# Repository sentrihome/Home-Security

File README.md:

# Home Security System — Full Architecture

Status: design draft — SoftAP shipping; Pi hub (`pi_hub`) barebones in repo; live/clips/Drive stubs pending full impl
Scope: end-to-end system — ESP32 hardware, provisioning, sensor pairing, security model, protocol specs, Pi/app/cloud product layer (alerts, live, clips), and known open items.
Merges: original ESP32 hardware architecture + `Local-First Architecture Storyboard` (mobile/, Pi, Tailscale, FCM/ntfy, Drive).
Pi software: Python SoftAP gate + one `pi_hub` process (not the retired Node `rasberry_pi_app` / cloud stack) — see **D20** and §13.

---
## Branch Naming Convention
Three types of tasks:
1. Rasberry Pi pie
2. ESP esp
3. Mobile app mob
Name of person working: firstname
Bitesized task: task

So the branch name will be: type-firstname-task

## Quick nav

| Section | Contents |
|---|---|
| [1](#1-system-overview) | System overview & diagram |
| [2](#2-hardware--component-roles) | Every component's role |
| [2.1](#21-esp32-architecture-diagram) | ESP32 hardware diagram — networks, UART, credential flow |
| [3](#3-decision-log) | Locked product choices |
| [4](#4-console-provisioning-flow) | Phone → console WROOM → S3 → home WiFi |
| [5](#5-sensor-pairing-flow) | Phone → sensor → console WROOM |
| [6](#6-default-ap-credentials-setup-time) | Anti-eavesdropping setup credentials |
| [7](#7-credential--key-model) | The three secrets, who holds what |
| [8](#8-failure-handling-provisioning) | WiFi connect failure/retry |
| [9](#9-uart-protocol-wroom--s3) | Frame format, command set |
| [10](#10-setup-ap-encryption) | WPA2 requirement on all setup APs |
| [11](#11-psk-recovery--backup) | Pi as PSK backup, tied to §16 |
| [12](#12-reboot--reconnect-behavior) | Console/S3/sensor reboot handling |
| [13](#13-pi-setup--product-hub) | SoftAP gate → `pi_hub` (live/clips); how it works & deploy |
| [14](#14-intruder-alerts-android-fcm--ios-ntfysh) | FCM (Android), ntfy.sh (iOS) |
| [15](#15-on-demand-livestream-tailscale) | Live only while app is open |
| [16](#16-pi--s3-link-confirmed-endpoints-transport-tbd) | Confirmed Pi↔S3 endpoints; transport still TBD |
| [17](#17-clips-pi-cache--google-drive) | Clip capture, cache, upload, playback |
| [18](#18-google-token-handoff) | OAuth refresh token to Pi |
| [18.1](#181-what-the-pi-needs-phone--pi-contract) | Locked JSON contract for the phone handoff |
| [19](#19-motion-event-pipeline-partially-resolved) | Camera confirmed Pi-only; alert-pipeline scope still open |
| [20](#20-arm--disarm-state-machine) | State ownership, authorization, entry/exit, sensor behavior |
| [21](#21-out-of-scope) | Explicit non-goals |
| [22](#22-open-items) | Full consolidated list |
| [23](#23-physical--manufacturing-notes) | Enclosure & label handling |

---

## 1. System Overview

Three physical subsystems, tied together by two links that are fully specified and one that is not yet:

```mermaid
flowchart TB
  subgraph sensors [Sensor Network]
    Sen1[Sensor WROOM]
    Sen2[Sensor WROOM]
  end

  subgraph console [Central Console]
    CW[Console WROOM<br/>AP + hub]
    S3[ESP32-S3<br/>station, display]
    Sen1 -->|WiFi, sensor_key auth| CW
    Sen2 -->|WiFi, sensor_key auth| CW
    CW <-->|UART, framed| S3
  end

  subgraph home [Home LAN / Cloud Layer]
    Pi[Raspberry Pi<br/>static IP, health, alerts, live, clips]
    FCM[FCM - Android]
    Ntfy[ntfy.sh - iOS]
    Drive[Google Drive]
    TS[Tailscale]
    S3 -.->|§16, endpoints confirmed<br/>transport TBD| Pi
    Pi -->|motion| FCM
    Pi -->|motion| Ntfy
    Pi --> Drive
    Pi <--> TS
  end

  subgraph phone [Mobile App]
    App[React Native app]
    FCM -->|tap| App
    Ntfy -->|tap/open| App
    App <-->|setup, live, clips| Pi
    App -.->|setup| CW
  end
```

**Fully specified today:** sensor ↔ console WROOM (WiFi + `sensor_key`), console WROOM ↔ S3 (UART, framed), phone ↔ Pi (SoftAP setup, health check, Tailscale, OAuth handoff, FCM/ntfy targets, Drive playback).

**Confirmed but not yet fully specified:** S3 ↔ Pi. The endpoints are settled — this is a direct Pi↔S3 link, not routed through the WROOM (§16, §20) — but the transport mechanism (static IP / mDNS / hybrid), framing, and auth are still open. Everything downstream of it (motion-triggered alerts reaching the Pi, PSK backup reaching the Pi, the PIN-set flow) depends on this transport being finalized.

---

## 2. Hardware & Component Roles

| Component | Role | WiFi / Network Mode | Responsibilities |
|---|---|---|---|
| ESP32-S3 | Central console | Station (home WiFi) | Display, keypad (PIN entry for disarm — see §20), stores home WiFi creds, stores sensor keys, **stores the disarm PIN in NVS**, relays credentials/status to console WROOM over UART. Motion/event relay toward Pi confirmed required — see §16, §20. |
| ESP32-WROOM (console-side) | Sensor hub / pairing surface | Access Point (persistent, currently `"espwifi"` — SSID string is not a hard spec requirement, any static value works) | Hosts sensor network, relays sensor data to S3 via UART, validates sensor auth (`sensor_key`), generates pairing credentials and the sensor-network PSK |
| ESP32-WROOM (sensor units) | Sensors | Station → connects to console WROOM's AP | Motion/door/etc. detection, sends events authenticated with `sensor_key`. One of two motion-alert triggers, alongside the Pi's camera detector — see §19. |
| Raspberry Pi | Setup relay, PSK backup, product hub | AP (setup only) → Station (post-setup, static IP `192.168.0.236`) | **Initializes first, before console provisioning — see §4, §13.** SoftAP then **`pi_hub`** on `:4000`. Owns the camera; OpenCV person detection (§19); FCM/ntfy alerts; WebRTC live; Drive clip upload; PSK backup pending §16 |
| Mobile App (React Native, `mobile/`) | Orchestrator / client | N/A | Walks the user through both the Pi setup flow and the console/sensor provisioning flow, holds home WiFi creds in memory only during setup, stores the sensor-network PSK for future pairing, saves the Pi host, registers for push (FCM/ntfy), handles Google OAuth and hands the refresh token to the Pi, plays live (via Tailscale) and clips (via Drive) |

**Confirmed: no camera on any ESP32.** The camera is Pi-attached only. It is no longer monitoring-only: the Pi runs OpenCV person detection on the camera feed as a second, independent motion-alert trigger alongside the ESP32 sensor network. See §19.

**Confirmed: the console has a physical keypad**, used for PIN entry on disarm (§20). **The PIN itself is stored in S3 NVS**, not on the Pi — this creates a flagged tension with the Pi-as-state-authority decision, see §20. **No local audio/siren hardware is planned for initial release** — the console is display + keypad only; Bluetooth speaker support (as a post-launch siren option) is roadmap, not v1.

**Key architectural point:** the console WROOM's AP is *not* home WiFi — it's a separate, persistent local network (currently named `"espwifi"`, but the name itself isn't a spec requirement — see §22 item 6 for the planned move to per-unit SSIDs) that only the S3 (via UART) and paired sensors ever touch. The S3 never joins this network over WiFi. Separately, the Pi runs on the actual home LAN with its own static IP, reachable by the phone directly and, once §16 is resolved, by the S3.

### 2.1 ESP32 Architecture Diagram

```mermaid
flowchart TB
  Phone([Mobile App])
  Router{{Home WiFi Router}}

  subgraph HomeNet [" Home WiFi — station side "]
    S3[ESP32-S3<br/>Central Console<br/>Station + Display + Keypad]
    NVSs[(S3 NVS<br/>home WiFi creds<br/>sensor_keys, disarm PIN)]
  end

  subgraph HSNet [" Console WROOM's Persistent AP — WPA2, SSID not spec-fixed "]
    CW[ESP32-WROOM<br/>Console Hub]
    NVSc[(WROOM NVS<br/>sensor PSK<br/>paired sensor_keys)]
    CW --- NVSc

    Sensor1[Sensor WROOM 1]
    Sensor2[Sensor WROOM 2]
    SensorN[Sensor WROOM ... up to 10]
  end

  Phone -. "1. setup: home WiFi creds<br/>over unique-per-unit setup AP" .-> CW
  CW == "2. UART, framed<br/>home WiFi creds" ==> S3
  S3 -- "2. store" --> NVSs
  S3 -- "3. join as station" --> Router
  S3 == "4. UART: connection result" ==> CW
  CW -. "5. sensor-network PSK<br/>generated, sent to phone" .-> Phone

  Phone -. "6. pairing: PSK + sensor_key<br/>over sensor's own setup AP" .-> Sensor1
  Sensor1 -- "WiFi + sensor_key auth" --> CW
  Sensor2 -- "WiFi + sensor_key auth" --> CW
  SensorN -- "WiFi + sensor_key auth" --> CW

  CW == "ongoing: sensor event relay" ==> S3

  classDef dashed stroke-dasharray: 5 5;
  class Phone dashed;
```

**Reading the diagram:**
- **Dashed arrows** — one-time setup/pairing traffic over a temporary WPA2 setup AP (§4, §5, §6).
- **Double solid arrows (`==`)** — the framed UART link between WROOM and S3 (§9), carrying both provisioning handoff and ongoing sensor-event relay.
- **Single solid arrows** — persistent WiFi connections: sensors to the console WROOM's AP (network-level PSK + application-level `sensor_key`, §7), and the S3 to the home router.
- **Two distinct WiFi networks, never bridged over the air:** home WiFi (S3 only) and the console WROOM's persistent AP network (WROOM + sensors — SSID currently `"espwifi"`, not a fixed spec value). The only link between them is the physical UART trace inside the enclosure (§23).

---

## 3. Decision Log

| ID | Decision | Choice | Notes |
|---|---|---|---|
| D1 | Mobile client | React Native Expo app in `mobile/` | Dev/prod build for push; not Expo Go |
| D2 | Android alerts | `expo-notifications` + FCM | Pi sends FCM on motion |
| D3 | iOS alerts | Public ntfy.sh | Secret topic; no Tailscale required for the buzz |
| D4 | Livestream path | Tailscale to Pi | On-demand, only while app is open |
| D5 | Alert transport | No persistent WebSocket | FCM / ntfy wake the user instead |
| D6 | Clip storage | Pi cache → Google Drive | App reads Drive; no Tailscale needed for clips |
| D7 | Drive auth | Phone Google OAuth → refresh token handed to Pi | Not password-based; `drive.file` scope only |
| D8 | Remote product tunnel | Tailscale (not ngrok/Cloudflare as product) | ngrok OK for ad-hoc dev only |
| D9 | Pi ↔ S3 discovery/transport | Endpoints confirmed (Pi ↔ S3 direct); mechanism **TBD** | mDNS or static IP — see §16 |
| D10 | Cloud S3 / cloud-backend clips | Retired as a product path | Local-first + Drive instead |
| D11 | Sensor-network auth | WiFi PSK (network-level) + `sensor_key` (application-level) | See §7 |
| D12 | Sensor AP fallback on disconnect | None — physical reset only | Prevents jamming-based sensor knockout, see §12 |
| D13 | Setup AP credentials | Unique per unit (batch-derived minimum, MAC-HMAC preferred) | Prevents shared-default eavesdropping, see §6 |
| D14 | Home WiFi credential storage | S3 NVS only | WROOM relays over UART but never persists home WiFi creds — see §7, §2.1 |
| D15 | Camera hardware | Pi-attached only, no ESP32 has a camera | See §2, §19 |
| D16 | UART frame format | `SYNC(2B) \| CMD(1B) \| LEN(2B) \| PAYLOAD \| CRC(1-2B)`, bidirectional | Locked before coding — see §9 |
| D17 | Sensor-network PSK lifecycle | Never regenerated on WROOM reboot — persists across reboots | Regenerating would force re-pairing every paired sensor, see §12 |
| D18 | UART link security | Plaintext, trusted via physical enclosure only | Accepted risk given enclosed PCB, not link-layer encrypted — see §9, §23 |
| D19 | "Encrypted SSID" terminology | Means a high-entropy random **PSK**, not literal SSID encryption | SSIDs broadcast in cleartext regardless — see §7 |
| D20 | Pi product software | **Python SoftAP + one `pi_hub` process** (Flask); do **not** revive Node `rasberry_pi_app` or cloud `:3001` as product | SoftAP is the boot gate; live + clips share one process so they don't fight over `/dev/video0`. Old Node pushed HLS/clips to cloud — local-first serves HLS from Pi and uploads clips to Drive. Code: `rasberry-pi-setup/`. See §13 |

---

## 4. Console Provisioning Flow

Goal: get the S3 onto home WiFi and generate the sensor-network PSK, using the phone as a one-time relay. **Confirmed: this runs after Pi initialization (§13) — Pi setup happens first in the unified onboarding flow.**

1. User enters home WiFi SSID + password once in the app. Held in memory only — never persisted to disk.
2. Phone connects to the console WROOM's setup AP (unique per-unit credentials, WPA2-secured — §6, §10).
3. Phone sends the home WiFi SSID/pass to the WROOM.
4. WROOM relays the credentials to the S3 over UART (framed — §9).
5. S3 attempts to join home WiFi as a station, bounded timeout (~9s), signaled on `IP_EVENT_STA_GOT_IP` (not `WIFI_EVENT_STA_CONNECTED` — association without a leased IP must not report success).
6. S3 reports the connection result (success or specific failure reason) back to WROOM over UART.
7. On success: WROOM generates a random, high-entropy sensor-network PSK (§7), if not already generated on first boot. SSID is a static, fixed string (`"espwifi"`) — not MAC-derived (see §22 item 6 for the planned move to per-unit SSIDs). Brings up its persistent AP under these credentials and sends the PSK back to the phone over the still-open setup link.
8. Phone stores the PSK for future sensor pairing. WROOM's setup AP closes / transitions to sensor-hub-only mode. **Currently commented out in firmware** for debugging — the setup AP is left running past this point so pairing traffic can be inspected/retried without a fresh flash cycle. Must be re-enabled before this leaves dev.
9. WROOM sends the PSK to the S3 over UART; the S3 pushes a copy to the Pi for backup (§16, Pi↔S3 link) — this step depends on §16's transport being finalized; it is not yet a working link.
10. On failure: see §8.

This is a one-time flow, not repeated per sensor.

---

## 5. Sensor Pairing Flow

Done once per sensor, any time after console provisioning, using the PSK the phone already has stored.

1. New sensor boots in AP mode, broadcasting its own unique per-unit setup AP (§6).
2. Phone connects to the sensor's setup AP.
3. Phone sends the console WROOM's sensor-network SSID + PSK to the sensor.
4. Sensor switches to station mode and connects to the console WROOM's persistent AP.
5. Sensor authenticates at the application layer using `sensor_key` (§7) — WiFi-level connection alone does not grant trust.
6. WROOM validates the `sensor_key`, marks the sensor as paired, stores the key in NVS, and begins relaying its events to the S3.

**Constraint — pairing requires the WROOM AP not be at capacity:** the same persistent AP serves both ongoing sensor traffic and new-sensor pairing. Confirmed system limit: sensor count will not exceed 10 (ESP32 SoftAP station cap). App should check station count before initiating pairing and prompt the user if the AP is at or near capacity (exact UX not yet finalized — §22).

---

## 6. Default AP Credentials (Setup-Time)

**Current state: hardcoded shared default.** All units currently ship with the same fixed setup AP credentials, baked into firmware — not per-unit, not batch-derived. This reopens the eavesdropping window the design intends to close: anyone who knows the shared default (e.g. from a leaked unit, teardown, or public firmware) could intercept home WiFi or PSK credentials on any other unit's setup AP during provisioning.

**Planned: unique-per-unit credentials**, not a shared default — this is the fix for the above. Target approach: batch-unique credentials at minimum (shipped per manufacturing batch), with an upgrade path to fully per-device derived credentials:

```
ap_password = HMAC(batch_secret, MAC_address) → encode → print on label/QR
```

No provisioning database required — each unit would derive its own password locally and deterministically at boot from its own MAC address and a batch secret baked into firmware at flash time. Not yet implemented — see §22.

Requirements regardless of tier (apply today, independent of hardcoded-vs-derived):

- Setup AP is WPA2-secured using the current password — never open (§10).
- Setup AP auto-closes after a timeout (2–5 minutes) if no provisioning occurs.
- Re-entering setup/pairing mode after timeout requires a physical button press, not an always-available AP.
- The printed label/QR (once per-unit derivation lands) must not be visible on the outside of retail packaging (§23). Not applicable yet under the current shared-default state — there's nothing unit-specific to print.

---

## 7. Credential & Key Model

Four distinct secrets exist on the ESP32 side. They must not be conflated:

| Secret | Generated by | Purpose | Stored where |
|---|---|---|---|
| Home WiFi SSID/pass | User (typed once) | Lets S3 join home WiFi | S3 NVS only — WROOM does not persist it, only relays via UART |
| Sensor-network PSK | Console WROOM (random, high-entropy, 32-char alphanumeric via `esp_random()`) | WPA2 password for the WROOM's persistent AP | Phone app (primary), Pi (backup — pending §16), WROOM NVS |
| `sensor_key` | Console WROOM, generated uniquely per sensor during pairing | Application-layer authentication of each sensor after WiFi connection | WROOM NVS (per paired sensor), sensor's own NVS |
| Disarm PIN | User, set via the mobile app | Authorizes disarm from the console keypad or the app — see §20 | **S3 NVS.** This is the odd one out: unlike the other three, it's not device-provisioning material, and its storage location creates a flagged tension with the Pi being the arm/disarm state authority — see §20. |

**Why `sensor_key` matters:** the sensor-network PSK is shared across all paired sensors — anyone who obtains it could join the WiFi network. `sensor_key` prevents an arbitrary WiFi-connected device from impersonating a sensor; the WROOM only accepts data from sensors presenting a valid, previously-issued key.

A parallel pattern exists on the product side: the Drive OAuth **refresh token** (§18) is a fifth secret, phone-mediated to the Pi the same way the PSK is phone-mediated to sensors — see §22 for the open question of unifying these into one "phone → device secret handoff" primitive.

Terminology note: nothing here is literal SSID encryption — SSIDs broadcast in cleartext regardless. What's unique/high-entropy is the **PSK** and the **`sensor_key`**, not the SSID (which can simply be MAC-derived and unique).

---

## 8. Failure Handling (Provisioning)

**Confirmed: binary outcome only.** The S3 reports `wifiConnection: true` or `wifiConnection: false` over UART — no reason code is surfaced to the WROOM, the phone, or the app. Wrong password, SSID not found, weak signal, and any other `WIFI_EVENT_STA_DISCONNECTED` cause all collapse to the same `false`. The app's only recourse on failure is to let the user retry.

`wifi_event_sta_disconnected_t->reason` is captured firmware-side (S3) at the point of disconnect but intentionally not forwarded over UART or wired into any command — available for future use if reason-level UX is ever built, but out of scope now.

Rules:

- Setup AP (WROOM or Pi) stays alive across a failed attempt — not torn down until success is confirmed.
- No retry cap on the S3's underlying `esp_wifi_connect()` reconnect loop — it retries indefinitely on disconnect. This is by design: a `false` result has already reached the phone, so the user can re-enter credentials and trigger a fresh attempt at any time; capping retries and requiring a physical button adds friction without a corresponding safety need here (contrast §12's sensor reconnect, where the no-fallback cap is a deliberate anti-jamming measure, not a UX one).

---

## 9. UART Protocol (WROOM ↔ S3)

Bidirectional framing required — both directions carry meaningful payloads.

```
[SYNC: 0xAA 0x55] [CMD: 1B] [LEN: 2B] [PAYLOAD: N bytes] [CRC: 1-2B]
```

Minimum command set to define before coding:

- `WROOM → S3`: home WiFi SSID/pass payload
- `S3 → WROOM`: connection result (success / specific failure reason)
- `WROOM → S3`: sensor event relay (post-pairing, ongoing telemetry)
- `S3 → WROOM`: commands (arm/disarm, etc.) to be relayed onward to sensors
- `S3 → WROOM`: status/heartbeat
- **`WROOM → S3`: motion/event notification tagged for Pi relay** — new command needed once §16's transport lands; distinct from routine telemetry if it needs different urgency/handling given the alert latency budget (§16)

**Flagged ambiguity:** the "commands relayed onward to sensors" line above implies each sensor is told the current arm state directly. But §20 states sensors "relay to the Pi only while armed," and the "sensor event relay" line above describes WROOM→S3 telemetry as unconditional/ongoing — these two aren't obviously the same design. Not yet decided: does arm/disarm state propagate all the way to each sensor (so a disarmed sensor stops transmitting entirely — relevant for battery life, §22 item 10), or do sensors always transmit and the WROOM/S3/Pi layer decides whether to act on it? Added to Open Items (§22).

The disarm PIN does **not** need a UART command — it's confirmed to travel `Pi → S3` directly (§16, §20) and never touches the WROOM.

Without framing, a byte-stream split across two reads on either side will silently corrupt credential or event payloads — this must be a checksummed, framed protocol.

Trust assumption: this UART link is internal to an enclosed PCB inside the house; physical access implies the system is already compromised, so plaintext credentials on this link are an accepted risk given the enclosure.

---

## 10. Setup AP Encryption

All temporary setup APs (Pi, console WROOM, sensor WROOMs) must run WPA2 using their unique per-unit password (§6) — never open. An open setup AP would let anyone in range passively sniff home WiFi credentials and the sensor-network PSK regardless of how unguessable the SSID is. Unique SSID ≠ encryption.

---

## 11. PSK Recovery / Backup

The phone app is not the sole holder of the sensor-network PSK. A backup copy should be pushed to the Raspberry Pi once both are on home WiFi.

**This depends on §16 (Pi↔S3 link), whose endpoints are now confirmed but transport/auth is still undesigned.** Do not build a one-off transport just for this — once §16's transport and auth are chosen, reuse them for the PSK backup push rather than inventing a second channel.

Open items:

- Push vs. pull, and behavior if the Pi is offline or unprovisioned when the PSK is generated — console/sensor setup should not block on Pi availability.
- Whether the Pi is required for day-to-day operation or purely a setup/recovery aid. Current intent: console and sensors keep operating autonomously if the Pi is off or removed — but §16 makes the *alerting* path (not sensor operation) look Pi-dependent. See §16.

---

## 12. Reboot / Reconnect Behavior

- **Console WROOM reboot:** AP credentials restored from NVS immediately on boot — same SSID/PSK, never regenerated (sensors already hold the old ones and would need re-pairing otherwise). Sensor data buffered by WROOM if the S3 link is briefly down, capped queue (e.g., 50 messages), dropping oldest on overflow.
- **S3 reboot:** WROOM's AP and sensor connections unaffected. WROOM buffers sensor events until UART with the S3 resumes.
- **Sensor loses connection to console:** sensor retries using the console's MAC address (not IP) with exponential backoff. **No automatic fallback to AP mode** — deliberate, to prevent a jamming attack from forcing sensors into a re-pairable, disconnected state (e.g., disabling motion detection). Re-entering pairing/setup mode requires a physical action (button hold).

---

## 13. Pi Setup & Product Hub

The Pi runs its own independent SoftAP-based setup flow (implemented under `rasberry-pi-setup/`), separate from the console's provisioning in §4. **Confirmed: this runs first in the unified onboarding flow** — the console's setup (§4) happens after Pi initialization completes, not in parallel and not the other way around.

**D20 (locked):** keep SoftAP in Python; run live + clips + Drive as modules of **one** hub process (`pi_hub`). Do not bring back the old Node `rasberry_pi_app` / cloud-backend split as the product path. SoftAP is the **network gate**; the hub starts only after home Wi‑Fi is up. SoftAP and hub never both bind `:4000`.

### How it works

```
Boot → pi-setup.service → pi-setup-boot.sh
         │
         ├─ no / bad Wi‑Fi  → SoftAP HomeSecurity-Setup + pi-setup-api.py :4000
         │                     (GET /status, /scan, POST /wifi)
         │                     hub stopped; .hub-ready removed
         │
         └─ Wi‑Fi OK at 192.168.0.236
                              → touch ~/homesecurity/.hub-ready
                              → systemctl start pi-hub
                              → one Flask process :4000 (live + clips + Drive)
```

| Piece | Kind | When |
|--------|------|------|
| `pi-setup-boot.sh` + SoftAP API | bash + small Flask | Always / unconfigured |
| `pi_hub` (`app.py` + `live` / `clips` / `drive`) | one Python app | Configured + on LAN |
| ffmpeg | subprocess from `live` / `clips` | On demand — not a separate daemon |

**Onboarding steps (product):**

1. Unconfigured Pi boots SoftAP (`HomeSecurity-Setup`).
2. User joins SoftAP; app sends home WiFi credentials (`POST /wifi`).
3. Pi joins home LAN at static IP `192.168.0.236`.
4. App verifies hub (`GET /health` → `mode: "hub"`), saves Pi host.
5. User installs Tailscale on Pi and phone (same tailnet); MagicDNS or `100.x` for live (§15).
6. *(Future)* App pairs a long-lived device token with the Pi for API auth — recommended to also auth §16 PSK backup.

**Hub API (after Wi‑Fi; stubs in repo, full ffmpeg/Drive TBD):**

| Method | Path | Module |
|--------|------|--------|
| GET | `/health` | hub (`mode: hub`) |
| POST | `/start` `/stop` | `pi_hub.live` — on-demand HLS |
| POST | `/motion` | `pi_hub.clips` → `pi_hub.drive` |
| POST | `/auth/drive` | `pi_hub.drive` — refresh token from app |
| GET | `/hls/<file>` | HLS playlist/segments |

Repo layout: `rasberry-pi-setup/pi_hub/`, units in `rasberry-pi-setup/systemd/`. Detail + troubleshooting: [`rasberry-pi-setup/PI-SOFTAP-README.md`](rasberry-pi-setup/PI-SOFTAP-README.md).

### Deploying changes to the Pi

**CI (every push under `rasberry-pi-setup/`):** GitHub Actions workflow [`.github/workflows/pi-deploy.yml`](.github/workflows/pi-deploy.yml) SSHs to the Pi (via Tailscale when `TS_AUTHKEY` is set), `git fetch` + checkout of that commit, runs `rasberry-pi-setup/scripts/ci-pull-deploy.sh` (install + restart `pi-hub`). Secrets and one-time Pi bootstrap: [`PI-SOFTAP-README.md`](rasberry-pi-setup/PI-SOFTAP-README.md) → **CI deploy**.

**Manual from a LAN machine** (Pi at `192.168.0.236`, user `koushik`):

```bash
cd rasberry-pi-setup
./deploy-to-pi.sh
# optional: PI_IP=192.168.0.236 PI_USER=koushik ./deploy-to-pi.sh
```

What that does:

1. Copies SoftAP scripts, `pi_hub/`, `systemd/*.service`, and `requirements.txt` to `/tmp/rasberry-pi-setup` on the Pi.
2. Runs `sudo ./install-pi-setup.sh` on the Pi — installs deps (Flask, ffmpeg, jq), copies files to `/home/koushik/`, installs systemd units, enables `pi-setup.service`.
3. Hub is **not** auto-enabled for multi-user boot by itself; `pi-setup-boot.sh` starts `pi-hub` only after home Wi‑Fi succeeds.

**After manual deploy:**

```bash
ssh koushik@192.168.0.236 'sudo reboot'   # clean SoftAP → hub handoff
# once on home Wi‑Fi:
curl http://192.168.0.236:4000/health     # expect "mode":"hub"
```

**Iterate without full reinstall** (hub code only, Pi already provisioned):

```bash
scp -r rasberry-pi-setup/pi_hub koushik@192.168.0.236:/home/koushik/
ssh koushik@192.168.0.236 'sudo touch /home/koushik/homesecurity/.hub-ready && sudo systemctl restart pi-hub'
```

**Logs:** SoftAP → `tail -f /var/log/pi-setup.log` · Hub → `journalctl -u pi-hub -f`

### Test protocol

| # | Step | Expected |
|---|---|---|
| 13.1 | Pi in SoftAP or already on LAN | Setup screen usable |
| 13.2 | Complete SoftAP creds; phone on home WiFi | `GET http://192.168.0.236:4000/health` succeeds with `mode: hub` |
| 13.3 | Kill and reopen app | Saved Pi host still present |
| 13.4 | Tailscale connected on Pi and phone | Both show in `tailscale status`; ping works |
| 13.5 | **Fail:** phone on cellular, Tailscale off, hit LAN IP | Health fails; clear "unreachable" UI, not a hang |

**Failure modes:** SoftAP scan fails → not on `HomeSecurity-Setup`. Health 404/timeout → hub not started or still in SoftAP-only mode. Wrong subnet → static IP mismatch. Port conflict → SoftAP API and hub both tried to bind `:4000` (boot script should prevent this).

---

## 14. Intruder Alerts: Android (FCM) & iOS (ntfy.sh)

No persistent WebSocket for alerts (D5) — push services wake the user instead.

### Android — FCM

1. Dev/prod build registers for push (`expo-notifications` + FCM).
2. App sends its FCM device token to the Pi (LAN or Tailscale) once paired.
3. On motion, Pi POSTs to FCM with title/body (and optional deep-link data).
4. OS shows a lock-screen notification.
5. Tap → app opens (Live or Alerts screen).

**Failure modes:** Expo Go used → push unreliable/wrong app id. Token never uploaded → Pi has nothing to target. Pi's outbound network to Google blocked → send fails silently unless logged.

### iOS — ntfy.sh

1. Generate a high-entropy secret topic (treat like a password); store on Pi, show once in app Settings.
2. User subscribes to `https://ntfy.sh/<topic>` (ntfy iOS app for v1).
3. On motion, Pi POSTs to `https://ntfy.sh/<topic>`.
4. User sees the notification; opens the app when ready.
5. Live still requires Tailscale (§15) — ntfy carries no video.

**Failure modes:** topic leaked → strangers can spam or snoop titles. ntfy.sh outage → no iOS buzz (LAN live still works independently). User never subscribed → silent miss.

### Combined test targets

Motion → notification within **≤ 15 seconds** on both platforms. This budget matters directly for §16 — see the latency note there.

---

## 15. On-Demand Livestream (Tailscale)

Live only while the app is open — no background streaming.

1. User opens the app (often from an FCM/ntfy tap).
2. App resolves the Pi's base URL: prefers Tailscale host when off-LAN, else saved LAN IP.
3. Optional `POST /start`, then play HLS from the Pi.
4. User leaves the Live screen → stop requesting segments; no persistent socket.
5. If Tailscale is disconnected → clear error: enable Tailscale or join home WiFi.

**Failure modes:** playing the LAN IP while away → timeout. Firewall/CGNAT rare with Tailscale but DERP relay may add latency. Heavy cellular data usage — warn in UI if needed.

---

## 16. Pi ↔ S3 Link (Confirmed Endpoints, Transport TBD)

**Status: endpoints confirmed, transport/framing/auth still undesigned.** This is the single biggest remaining gap connecting the ESP32 hardware architecture to the product layer.

**Confirmed: this link connects the Pi directly to the S3** — not the WROOM. Consistent with the rest of this document's topology (§1, §2.1), the S3 is the only ESP32 with home-LAN reachability; the WROOM has no home-WiFi connectivity and is not involved in Pi-facing traffic. The WROOM's role remains limited to the isolated sensor-network AP and UART with the S3.

Everything downstream depends on this link:

- §11's PSK backup push (S3 → Pi, sourced from the WROOM via UART, then relayed by S3)
- Motion-triggered alerts (§14) actually firing, confirmed required per §19's resolved motion-alert pipeline
- The PIN-set flow and arm/disarm coordination (§20), confirmed to route `Pi → S3` directly

### Candidates (not yet chosen)

| Option | Idea | Pros | Cons |
|---|---|---|---|
| Static IP | Pi stays at `192.168.0.236`; S3 configured with that IP | Simple; already assumed elsewhere in the Pi setup docs | Breaks if the subnet changes |
| mDNS | Pi advertises e.g. `homesecurity-pi.local` | No hard-coded IP | mDNS can be flaky on some routers / ESP network stacks |
| Hybrid | Static default + mDNS fallback | Resilient | More firmware and app work |

### What needs to be specified once a candidate is chosen

- **Transport & framing** for S3 → Pi messages (motion events, PSK backup), analogous to §9's UART framing.
- **Authentication** — should not be an unauthenticated push; anything on the LAN claiming to be "the Pi" (or "the console") must not be trusted by default. Recommended: reuse the "paired device token" mechanism already planned for phone↔Pi auth (§13, step 6) rather than inventing a third auth scheme.
- **Latency budget** — the alert path's ≤15s target (§14) has to cover sensor → WROOM (radio) → UART (WROOM→S3) → this link (S3→Pi) → Pi → FCM/ntfy → phone OS, end to end. Each hop needs its own bounded latency; there isn't much slack in 15 seconds once every hop is accounted for.
- **Availability behavior** — if this link is down (Pi off, rebooting, off the LAN), does the console have any fallback alerting path, or is a live Pi a hard dependency for every motion alert? This is currently undefined and should be decided explicitly rather than defaulting to "no alert."

---

## 17. Clips: Pi Cache → Google Drive

1. User signs into Google in the phone app (`access_type=offline`, `drive.file` scope).
2. App sends the refresh token (or auth code) + OAuth client id/secret + email to the Pi over LAN or Tailscale (§18).
3. On an event: Pi writes the clip to local cache (`homesecurity/clips/clip-*.mp4`), then uploads to Drive with a refreshed access token into an app-created **SentriHome** folder.
4. App lists/plays clips via Drive (the user's own session) — not via the Tailscale video tunnel.
5. Pi may prune the local cache after successful upload (retention policy TBD, §22 #9).

Pi implementation (`rasberry-pi-setup/pi_hub/drive.py`) is live: motion/detection already call `drive.upload_clip()`. Uploads stay private (`drive.file` only; no "anyone with the link"). They no-op with a loud error until the phone completes §18.

### Test targets

- Clip appears in Pi cache within budget after a triggering event.
- Clip appears in the user's Drive folder (`SentriHome`) after upload.
- Clips remain listable/playable from Drive with Tailscale fully off (cellular only) — this path must not depend on Tailscale.
- Revoked Google access → next upload fails loudly (`invalid_grant` on `GET /auth/drive`), app prompts re-auth (not a silent drop).

**Failure modes:** missing `prompt=consent` → no refresh token issued. Upload quota / Drive API errors. App signed into a different Google account than the one whose token lives on the Pi.

---

## 18. Google Token Handoff

```mermaid
sequenceDiagram
  participant App
  participant Google
  participant Pi
  participant Drive
  App->>Google: OAuth offline consent, drive.file scope
  Google-->>App: refresh_token + email
  App->>Pi: POST /auth/drive (LAN or Tailscale)
  Pi->>Pi: Store refresh_token encrypted at rest
  Pi->>Drive: Upload clip with refreshed access_token
  App->>Drive: List/play clips as the signed-in user
```

Rules:

- Hand off only over home LAN or Tailscale — never over a raw, unauthenticated public URL.
- Store on the Pi **encrypted at rest**; never write tokens to app logs or setup logs.
- Scope limited to `drive.file` — only files the app itself creates/manages, not full Drive access.
- Provide a revoke/re-auth path in Settings if uploads start failing.
- The OAuth **client_id and client_secret travel with the refresh token**. A refresh token cannot be used by a different Google Cloud client than the one that issued it, so the phone and the Pi must share one Web-application OAuth client.

This is the same "phone-mediated secret handoff to a persistent device" pattern as the sensor-network PSK (§7, §11) and, once designed, the §16 auth token — worth eventually converging on one shared primitive instead of three independently-built ones (§22).

Phone implementation guide (Expo template, Cloud Console steps, Settings UX): **[DOCUMENTATION.md — Phone: Google Drive OAuth](DOCUMENTATION.md#phone-google-drive-oauth-and-token-handoff)**.

### 18.1 What the Pi needs (phone → Pi contract)

`POST /auth/drive` on port 4000. JSON, one of:

| Field | Required | Notes |
|---|---|---|
| `refresh_token` | Shape A | Phone already exchanged the auth code |
| `auth_code` (alias `server_auth_code`) | Shape B | Pi exchanges it; send `code_verifier` if PKCE was used |
| `code_verifier` | Shape B + PKCE | Expo AuthSession default |
| `redirect_uri` | Shape B | Must match the Google Cloud authorized URI (default `homesecurity://oauth`) |
| `client_id` | **always** | Same Web client the phone used |
| `client_secret` | **always** | Same Web client the phone used |
| `email` | recommended | Pi fetches from userinfo if omitted |

`GET /auth/drive` returns `{ linked, email, folder_name, folder_id, last_upload, error }` and never the token. `DELETE /auth/drive` forgets it. `/health` includes the same object under `drive`.

---

## 19. Motion Event Pipeline (Resolved)

**Confirmed: no ESP32 (S3 or WROOM) has a camera.** The camera is Pi-attached only, matching the product-layer diagram's `Camera → Pi` line directly.

**Superseded: camera-based detection has shipped, ahead of the roadmap.** This section
previously stated the camera was monitoring/live-view only and that the ESP32 sensor network
was the system's **only** motion-alert trigger. That is no longer accurate. The Pi now runs
person detection on the camera feed (`rasberry-pi-setup/pi_hub/detect.py`: MobileNet-SSD via
OpenCV's DNN module, reading the shared MediaMTX RTSP path).

There are therefore **two independent triggers** into one clip/alert pipeline:

```
A) Sensor (WROOM) → Console WROOM (WiFi, sensor_key auth) → Console S3 (UART) → Pi (§16 link) ┐
                                                                                              ├→ clip + Drive upload → Notification (FCM/ntfy)
B) Camera → MediaMTX (RTSP) → Pi OpenCV detector (person-gated) ───────────────────────────────┘
```

Both converge on `pi_hub.events.handle_motion()`, so a camera detection and a manual/sensor
trigger produce byte-identical downstream behaviour. Trigger A still depends on §16 and its
≤15s latency budget (§14); trigger B is entirely local to the Pi and works even with §16
unresolved — which is why it shipped first.

**Detection is class-gated, not motion-gated.** Only labels in
`config.DETECT_TARGET_LABELS` (default: `person`) raise an event, and a cooldown window
suppresses repeat events. This is a deliberate false-positive strategy: a pet or a moving
curtain produces frames but not alerts, which is the failure mode naive frame-differencing
motion detection suffers from.

**Still open:** whether the camera detector should *corroborate or suppress* sensor-triggered
alerts rather than firing independently (e.g. sensor trip + no person seen → lower-confidence
alert). Today the two triggers do not consult each other. See §22.

---

## 20. Arm / Disarm State Machine

**Previously entirely missing from this document — this is the core logic that makes the system a security system rather than just a sensor/notification pipeline.** State ownership is now resolved; one new topology question has surfaced from that resolution and needs a call before implementation (see below).

### State ownership — resolved, with a flagged topology question

- **The Pi remains the source of truth for armed/disarmed *state*.**
- **Confirmed resolution: the S3 validates the PIN locally.** Round-tripping every disarm attempt through the Pi for validation was rejected as too slow — and the Pi doesn't hold the PIN anyway, so it couldn't validate even if asked to. The S3 checks the PIN against its own NVS and acts on it immediately; the Pi is informed/acknowledged afterward so its own arm/disarm state and alert-suppression logic stay in sync. This is resolution **(a)** from the previous draft of this section.

### Confirmed PIN-set flow

**Resolved: the Pi talks directly to the S3, not the WROOM** — consistent with the rest of this document's topology (§1, §2.1), where the S3 is the only ESP32 with home-LAN reachability.

When a user sets a disarm PIN via the mobile app:

```
Phone App → Pi → Console S3 (via §16 link, stored in S3 NVS)
```

Console S3 acknowledges receipt back through the same path once the PIN is stored, so the app can confirm the set succeeded. The WROOM is not involved in this flow at all — it doesn't hold the PIN and doesn't need to relay it.

This resolves the topology question raised in the previous revision of this document: §16 is confirmed as a **Pi ↔ S3** link, not Pi ↔ WROOM. No dual AP+STA capability is needed on the WROOM.

### Authorization

- **Arm**: mobile app or central console. **No PIN required.**
- **Disarm**: mobile app or central console. **PIN required**, checked against the PIN stored in S3 NVS. The user may set the same PIN for both paths, or different ones, via the mobile app.
- This is an intentionally asymmetric model — arming is low-friction, disarming has a deliberate check.

**Confirmed: the console has a physical keypad**, used to enter the PIN for a console-initiated disarm (also noted in §2).

### Entry/exit delay

- **None.** No grace period on entry or exit.
- **While armed:** a sensor trigger while armed relays the event through the pipeline below.
- **While disarmed:** sensors produce no relay and no alert (and no logging — see below).

### Confirmed motion-alert data flow

On a sensor trigger while armed, the event flows:

```
Sensor (WROOM) → Console WROOM → Console S3 (UART) → Pi (§16 link) → Notification System (FCM/ntfy)
```

This is the same pipeline established in §19, terminating in a **phone push notification via the Pi**.

**Confirmed: no local audible/beep hardware is planned for initial release.** There is no buzzer, speaker, or siren on the console at launch — the phone push notification is the entire alert output for v1. **Planned post-release:** Bluetooth speaker pairing, allowing a user-supplied Bluetooth speaker to act as a local siren. This is a roadmap item, not part of the initial build — see §21 (Out of Scope) for the launch/post-launch boundary.

### Sensor behavior by arm state

- Sensors relay to the Pi (triggering a push notification) only while armed.
- **Confirmed: no logging while disarmed.** Disarmed-state sensor activity is not recorded anywhere. If a general event history/log is ever built (§22, item 13), it will only ever reflect armed-state activity, by design — this is worth keeping in mind if that feature gets built later, since it means the system has no record of activity that happened while disarmed.

### What this section does *not* yet cover

- Partial/zone arming (e.g., "arm perimeter only," "stay" vs. "away" modes common in commercial systems) — not requested, assumed out of scope unless specified otherwise.
- Auto-arm/auto-disarm based on schedule or geofencing — not mentioned, treated as a future feature if ever wanted.
- What happens to an **in-progress notification** if the system is disarmed mid-trigger — not yet specified, and now also depends on resolving the state-ownership tension above.

---

## 21. Out of Scope

| Item | Why |
|---|---|
| Persistent WebSocket / SSE for alerts | Replaced by FCM + ntfy (D5) |
| S3 / cloud-backend as clip or live CDN | Retired — local-first + Drive instead (D10) |
| Cloudflare Tunnel / ngrok as **product** remote access | Tailscale chosen (D8); ngrok OK for brief dev only |
| Sensor AP-mode fallback on disconnect | Explicitly rejected — jamming risk (D12) |
| Replacing the existing Pi SoftAP wizard | Keep SoftAP; extend with `pi_hub` after Wi‑Fi (D20) |
| Reviving Node `rasberry_pi_app` + cloud `:3001` as product | Retired — Python hub serves HLS locally and uploads clips to Drive (D10, D20); mine old Node only for ffmpeg ideas if found elsewhere |
| Relying on Expo Go for FCM | Push unreliable under Expo Go; use dev/prod builds |
| Local buzzer/siren hardware on the console (v1) | Confirmed: no beep/audio hardware planned for initial release — see §20 |
| Bluetooth speaker pairing as a local siren | Confirmed roadmap item, post-launch — not part of this design pass |

---

## 22. Open Items

Consolidated list, roughly in priority order for what blocks further design vs. implementation:

1. **§16 — link design (highest priority):** endpoints confirmed (Pi ↔ S3 directly), transport still needs choosing: static IP / mDNS / hybrid, plus framing and auth. Required for the confirmed alert pipeline (§19), the PIN-set flow (§20), and PSK backup (§11).
2. **§9/§20 — does arm/disarm state reach individual sensors?** Unclear whether sensors are told the arm state directly (stopping transmission entirely while disarmed) or always transmit while the WROOM/S3/Pi layer decides whether to act on it. Affects sensor battery life (item 10 below) and the exact UART command set.
3. **PSK backup auth**: confirm the §13 "paired device token" is meant to also authenticate the §11 PSK backup push (recommended, not yet stated).
4. **Re-provisioning vs. factory reset**: whether changing home WiFi (router replaced, password changed) and "forget all sensors" are the same physical action or distinct ones. **Explicitly deferred (TBD)** — not a near-term blocker.
5. **Sensor message integrity beyond `sensor_key`**: replay protection, if any sensor reading is ever used to drive an action rather than just display/log data.
6. **Multi-console households / MAC-derived SSID (planned, not yet implemented)**: SSID is currently a static string (`"espwifi"`) for every unit — fine for a single console, but indistinguishable between two consoles in one home. Planned fix: move to a MAC-derived SSID per unit (D19 already establishes this doesn't need to be high-entropy/secret, just unique — SSIDs broadcast in cleartext regardless).
7. **OTA update mechanism and signing**, once devices are in the field with unique per-device secrets.
8. **Pairing UX at the 10-sensor cap**: exact behavior when pairing is attempted while the WROOM AP is at or near capacity.
9. **Clip retention policy** on the Pi's local cache after a successful Drive upload.
10. **Unify the phone-mediated secret handoffs** (home WiFi creds → S3, sensor PSK → Pi, disarm PIN → S3, Drive refresh token → Pi) into one documented primitive rather than four separately-designed ones (§7, §18).
11. **System-wide gaps not yet designed at all**: sensor power/battery management, internet-outage alert fallback (what happens to alerting if home internet is down, since the whole pipeline routes through the Pi to FCM/ntfy), tamper detection, multi-user/multi-phone pairing, general event history/log (which, per §20, will only ever cover armed-state activity by design), and full Pi API authentication coverage. None of these have a home in this document yet.
12. **§6 — per-unit setup AP credential derivation (planned, not yet implemented)**: setup AP credentials are currently a hardcoded shared default across all units, not batch- or MAC-derived. Reopens the eavesdropping concern §6 was written to close. HMAC(batch_secret, MAC_address) approach is specified but not built — needs to land before manufacturing/label pipeline (§23) can proceed.

---

## 23. Physical / Manufacturing Notes

- Printed labels/QR codes carrying setup AP credentials must be inside the packaging (or under a peel-back sticker), not visible on the outer box — the label is a bearer secret once printed.
- UART lines between WROOM and S3 are treated as trusted only because the PCB is enclosed inside the house; this assumption breaks if the UART is ever exposed via an accessible debug header.

---

## Revision history

| Date | Change |
|---|---|
| 2026-08-18 | **Pi Drive upload shipped.** `pi_hub/drive.py` stores the phone-handed refresh token encrypted at rest (Fernet), refreshes access tokens, creates a `SentriHome` folder, and uploads event clips. `/auth/drive` is now GET/POST/DELETE; `/health` exposes `drive` status without secrets. Locked the phone→Pi JSON contract in §18.1 (`client_id`/`client_secret` required — refresh tokens are bound to the issuing OAuth client). Phone implementation guide: `DOCUMENTATION.md`. |
| 2026-08-13 | **Camera-based motion detection shipped, superseding the §19 "monitoring-only" decision.** `pi_hub/detect.py` runs MobileNet-SSD via OpenCV DNN against the shared MediaMTX RTSP feed (not `/dev/video0` — the single-publisher rule in §19/`camera.py` still holds) and raises person-gated events through the new `pi_hub/events.py`, the same pipeline `POST /motion` uses. Rewrote §19 around two independent triggers instead of one; updated §2 and the component table, which both still claimed the camera did no detection. Notable: this trigger is entirely local to the Pi, so it works with §16 still unresolved — the reason it shipped ahead of the sensor path. New open item in §19: the two triggers do not corroborate each other. Weights are sha256-verified at fetch time, not vendored. |
| 2026-08-02 | Consolidated ESP32 hardware architecture and Local-First Storyboard into a single full architecture document. Flagged §16 (ESP↔Pi link) and §19 (camera/motion ownership) as the two unresolved cross-cutting gaps. |
| 2026-08-02 | Confirmed: no camera on any ESP32 (S3 or WROOM) — camera is Pi-attached only. Updated §2 and §19 accordingly; narrowed §19 to the remaining open question of whether ESP32 sensor events also feed the alert pipeline. |
| 2026-08-02 | Added §20 (Arm/Disarm State Machine) — previously entirely undocumented. Captured: Pi as state authority, app/console arm with no PIN, app/console disarm requiring PIN, no entry/exit delay, armed-trigger beep. Flagged open questions: console PIN input hardware, beep vs. push semantics, disarmed-state logging. Renumbered §20-22 to §21-23 accordingly. |
| 2026-08-02 | Resolved several §20/§19/§13 open questions: confirmed console keypad (§2, §20); confirmed motion-alert pipeline terminates in a Pi-driven phone push, with the console beep as parallel local feedback (§19, §20); confirmed camera is monitoring-only for now, ESP32 sensor network is the sole motion-alert trigger, camera-based detection is post-launch (§19); confirmed Pi initializes before console provisioning (§4, §13). Updated Open Items (§22) to remove resolved items and add newly surfaced smaller gaps (PIN offline-fallback, console beep hardware). |
| 2026-08-02 | Confirmed: disarm PIN stored in S3 NVS (§7, §20) — creates a flagged tension with the Pi-as-arm/disarm-authority decision, needs explicit resolution before implementation. Confirmed: no local beep/siren hardware at launch; Bluetooth speaker siren support is a post-launch roadmap item (§20, §21). Confirmed: no event logging while disarmed (§20). Updated §2, §7, §21, §22 accordingly. |
| 2026-08-02 | Resolved PIN-validation ownership: S3 validates the PIN locally, Pi is informed afterward (§20). Confirmed PIN-set flow: Phone App → Pi → console WROOM → console S3, with acknowledgment back. Flagged a new topology inconsistency: this flow has the Pi talking to the WROOM directly, which conflicts with the WROOM's documented lack of home-LAN connectivity — needs resolution before §16 can be designed (§16, §20, §22 item 1, now top priority). Added conditional UART command for PIN relay/ack (§9). |
| 2026-08-02 | Resolved the topology question from the previous entry: **confirmed the Pi talks directly to the S3, not the WROOM.** Renamed §16 to "Pi ↔ S3 Link (Confirmed Endpoints, Transport TBD)." Removed the WROOM hop from the PIN-set flow (§20) and the conditional UART command it required (§9) — the disarm PIN never touches the WROOM. Updated D9, quick-nav, and all cross-references accordingly. Removed the now-resolved topology item from Open Items (§22). |
| 2026-08-02 | **Full-document audit for repeated/systemic issues.** Fixed: duplicated "Terminology note" paragraph in §7 (verbatim copy-paste artifact); stale §4 step 9 still saying the WROOM pushes the PSK to the Pi (contradicted the confirmed Pi↔S3-only topology, now corrected to WROOM→S3→Pi); stale §1 diagram/prose still framing the S3-Pi link as fully unspecified and labeled "Act 6" (updated to reflect confirmed endpoints, transport TBD); §2.1 diagram not reflecting the confirmed keypad/PIN-in-NVS hardware (added). Flagged a new open item: whether arm/disarm state propagates to individual sensors or is enforced centrally (§9, §22 item 2) — §9's "commands relayed onward to sensors" line and §20's "sensors relay only while armed" line don't obviously describe the same mechanism. Noted as a general pattern: diagrams in this document have repeatedly lagged behind text-level decisions and need a deliberate check on each revision, not just prose cross-references. |
| 2026-08-03 | **D20 — Pi software stack.** SoftAP stays Python; product features run as one `pi_hub` Flask process after home Wi‑Fi (live HLS + clips + Drive stubs). Explicitly rejected reviving Node `rasberry_pi_app` / cloud `:3001` as product. Expanded §13 with boot handoff, hub API table, and deploy instructions (`deploy-to-pi.sh`). Updated §2 Pi row, §21 out-of-scope, and `rasberry-pi-setup` docs. |
| 2026-08-15 | **§4/§8 — provisioning result firmware fix.** Confirmed the S3 must signal WiFi join result on `IP_EVENT_STA_GOT_IP`, not `WIFI_EVENT_STA_CONNECTED` — association without a leased IP was reporting false success, silently killing the §16 alert path with no error surfaced anywhere. Updated §4 step 5 timeout from ~15–20s to ~9s accordingly. Collapsed §8's reason-code failure table to a confirmed binary `true`/`false` outcome — disconnect reason is captured firmware-side but not forwarded over UART or into app UX. Retry cap dropped from §8's rules: S3's reconnect loop retries indefinitely by design, since the phone already receives `false` and can re-trigger the flow without a physical-button requirement. §9/D16 reviewed and confirmed unchanged — both already specified `SYNC: 0xAA 0x55`; the `'c'`/`'8'` sync bytes seen in review were a firmware bug, not a spec deviation. |
| 2026-08-15 | **§7 — PSK length.** Sensor-network PSK confirmed as 32-char alphanumeric (was ~20-char) — within the 63-char WPA2 PSK limit, higher entropy for the shared network secret. |
| 2026-08-15 | **§4 — SSID confirmed static, not MAC-derived.** WROOM's persistent AP SSID is a fixed string (`"espwifi"`) for now; MAC-derivation moved from §4 step 7 to a planned item under §22 item 6, scoped to solving multi-console SSID collisions later. No security impact per D19 — SSID uniqueness was never load-bearing, only the PSK is. |
| 2026-08-15 | **§4 step 8 — flagged as dev-only state.** Setup-AP-close/transition-to-hub-only is currently commented out in firmware for debugging (setup AP stays up past pairing so traffic can be inspected without reflashing). Documented as a known pre-ship gap, not a spec change — must be re-enabled before release. |
| 2026-08-15 | **§6 — confirmed setup AP credentials are currently a hardcoded shared default**, not batch- or MAC-derived. Per-unit derivation (`HMAC(batch_secret, MAC_address)`) moved to a planned item under §22 item 12 — reopens the eavesdropping window §6 exists to close until implemented; flagged as a manufacturing-pipeline (§23) dependency. |
| 2026-08-15 | **§2 — confirmed the console WROOM's persistent AP SSID name is not a hard spec requirement.** Doc previously named it `"HomeSecurity"` as if fixed; updated §2, §2.1 diagram, and diagram-reading notes to describe it generically (currently `"espwifi"`, any static value is acceptable). Does not affect §22 item 6 (per-unit/MAC-derived SSID), which remains the tracked planned change; this only removes the specific fixed-name requirement, not the uniqueness question. Pi's `"HomeSecurity-Setup"` SoftAP name (§13) is unaffected — separate device, separate flow. |

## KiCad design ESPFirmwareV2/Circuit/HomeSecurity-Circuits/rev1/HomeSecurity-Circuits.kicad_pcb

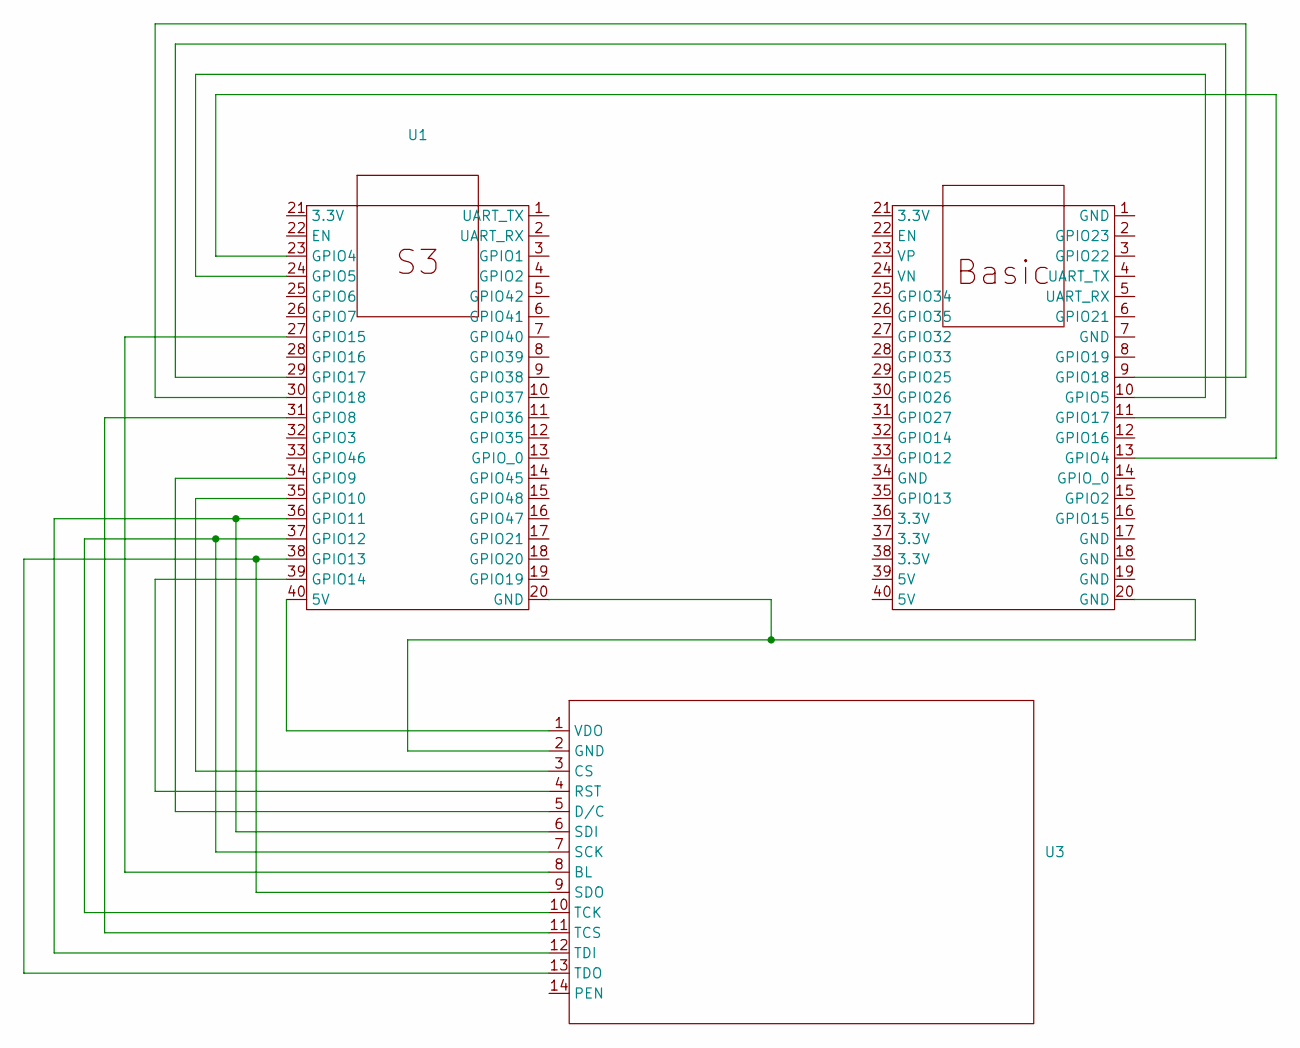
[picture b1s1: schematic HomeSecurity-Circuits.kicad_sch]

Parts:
U1, U2: esp32wroom
U3: ili9488

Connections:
unnamed: U1.40 (5V), U3.1 (VDO)
unnamed: U1.20 (GND), U2.20 (GND), U3.2 (GND)
unnamed: U1.23 (GPIO4), U2.13 (GPIO4)
unnamed: U1.24 (GPIO5), U2.10 (GPIO5)
unnamed: U1.31 (GPIO8), U3.11 (TCS)
unnamed: U1.34 (GPIO9), U3.5 (D/C)
unnamed: U1.35 (GPIO10), U3.3 (CS)
unnamed: U1.36 (GPIO11), U3.6 (SDI), U3.12 (TDI)
unnamed: U1.37 (GPIO12), U3.7 (SCK), U3.10 (TCK)
unnamed: U1.38 (GPIO13), U3.9 (SDO), U3.13 (TDO)
unnamed: U1.39 (GPIO14), U3.4 (RST)
unnamed: U1.27 (GPIO15), U3.8 (BL)
unnamed: U1.29 (GPIO17), U2.11 (GPIO17)
unnamed: U1.30 (GPIO18), U2.9 (GPIO18)

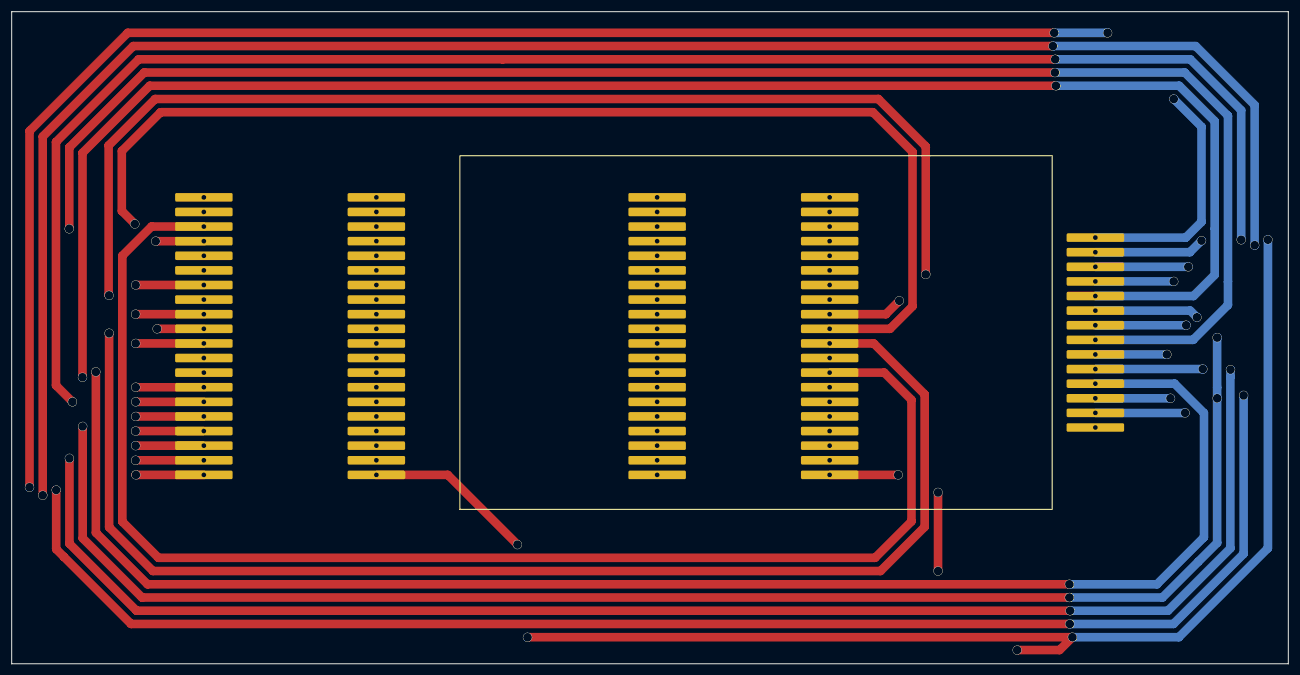
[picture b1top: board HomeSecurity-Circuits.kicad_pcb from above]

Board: 4 copper layers, 222.0 x 113.4 mm, 3 parts (0 on the bottom side), 14 nets.

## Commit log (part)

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2026-02-19 Initial plan
2026-02-23 Hackathon Completion
2026-02-28 Live streaming latency fix
2026-03-06 cleanup, removed trickle
2026-03-06 working low latency with trigger save
2026-03-23 Prototyping
2026-03-25 Reinitialize Central Console firmware development
2026-03-25 Clean up
2026-03-25 Screen component
2026-03-25 Screen component compile fix
2026-03-27 Display okay
2026-03-29 UI rehaul
2026-06-04 Start
2026-06-05 3d obj files
2026-06-09 Reboot'
2026-06-12 Display Configuration
2026-06-16 Change display, change of structure
2026-06-16 Added Ui transition from unarmed to armed and fixed screen coordinates. Initialized touch to correspond to actions
2026-06-16 Fixed a bug where going back from armed to disarmed state caused full screen rewrite
2026-06-16 Touch command feature added
2026-06-18 Codebase transition to ESPIDF
2026-06-29 Revise Wifi driver and solve reconnection issue
2026-06-30 Accesspoint Start
